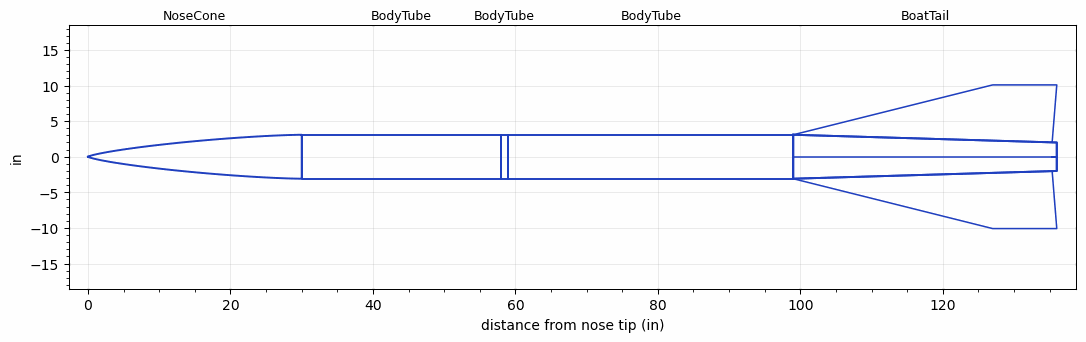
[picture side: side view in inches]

<RASAeroDocument>
 <FileVersion>2</FileVersion>
 <RocketDesign>
  <NoseCone>
   <Length>29.9999</Length>
   <Diameter>6.17</Diameter>
   <Shape>Von Karman Ogive</Shape>
   <Location>0</Location>
  </NoseCone>
  <BodyTube>
   <Length>28</Length>
   <Diameter>6.17</Diameter>
   <Location>29.9999</Location>
  </BodyTube>
  <BodyTube>
   <Length>1</Length>
   <Diameter>6.17</Diameter>
   <Location>57.9999</Location>
  </BodyTube>
  <BodyTube>
   <Length>40</Length>
   <Diameter>6.17</Diameter>
   <RailGuideDiameter>0.4715</RailGuideDiameter>
   <RailGuideHeight>0.44</RailGuideHeight>
   <Location>58.9999</Location>
   <BoattailLength>37</BoattailLength>
   <BoattailRearDiameter>4</BoattailRearDiameter>
  </BodyTube>
  <BoatTail>
   <Length>37</Length>
   <Diameter>6.17</Diameter>
   <RearDiameter>4</RearDiameter>
   <Location>98.9999</Location>
   <Fin>
    <Count>4</Count>
    <Chord>36.35</Chord>
    <Span>7</Span>
    <SweepDistance>28</SweepDistance>
    <TipChord>9</TipChord>
    <Thickness>0.25</Thickness>
    <Location>37</Location>
    <AirfoilSection>Rounded</AirfoilSection>
   </Fin>
  </BoatTail>
  <Surface>Smooth Paint</Surface>
  <ModifiedBarrowman>False</ModifiedBarrowman>
  <Turbulence>False</Turbulence>
  <UseBooster1>False</UseBooster1>
  <UseBooster2>False</UseBooster2>
 </RocketDesign>
 <LaunchSite>
  <Altitude>4595</Altitude>
  <Pressure>30.09</Pressure>
  <RodAngle>0</RodAngle>
  <RodLength>17</RodLength>
  <Temperature>90</Temperature>
  <WindSpeed>4.47</WindSpeed>
 </LaunchSite>
 <Recovery>
  <Altitude1>1000</Altitude1>
  <Altitude2>1000</Altitude2>
  <DeviceType1>Parachute</DeviceType1>
  <DeviceType2>Parachute</DeviceType2>
  <Event1>True</Event1>
  <Event2>True</Event2>
  <Size1>48</Size1>
  <Size2>144</Size2>
  <EventType1>Apogee</EventType1>
  <EventType2>Altitude</EventType2>
  <CD1>2.2</CD1>
  <CD2>0</CD2>
 </Recovery>
 <SimulationList>
  <Simulation>
   <SustainerEngine>O5500X  (AT)</SustainerEngine>
   <SustainerLaunchWt>79.5</SustainerLaunchWt>
   <SustainerNozzleDiameter>3.5</SustainerNozzleDiameter>
   <SustainerCG>90.9</SustainerCG>
   <SustainerIgnitionDelay>0</SustainerIgnitionDelay>
   <Booster1SeparationDelay>0</Booster1SeparationDelay>
   <Booster1IgnitionDelay>0</Booster1IgnitionDelay>
   <IncludeBooster1>False</IncludeBooster1>
   <Booster2Delay>0</Booster2Delay>
   <IncludeBooster2>False</IncludeBooster2>
   <TimetoApogee>38.89948</TimetoApogee>
   <MaxAltitude>28901.11</MaxAltitude>
   <MaxVelocity>1945.54</MaxVelocity>
   <OptimumWt>46.70626</OptimumWt>
   <OptimumMaxAlt>46.70626</OptimumMaxAlt>
  </Simulation>
  <Simulation>
   <SustainerLaunchWt>78.9966</SustainerLaunchWt>
   <SustainerCG>106.0928</SustainerCG>
   <SustainerIgnitionDelay>0</SustainerIgnitionDelay>
   <Booster1SeparationDelay>0</Booster1SeparationDelay>
   <Booster1IgnitionDelay>0</Booster1IgnitionDelay>
   <IncludeBooster1>False</IncludeBooster1>
   <Booster2Delay>0</Booster2Delay>
   <IncludeBooster2>False</IncludeBooster2>
  </Simulation>
 </SimulationList>
</RASAeroDocument>
